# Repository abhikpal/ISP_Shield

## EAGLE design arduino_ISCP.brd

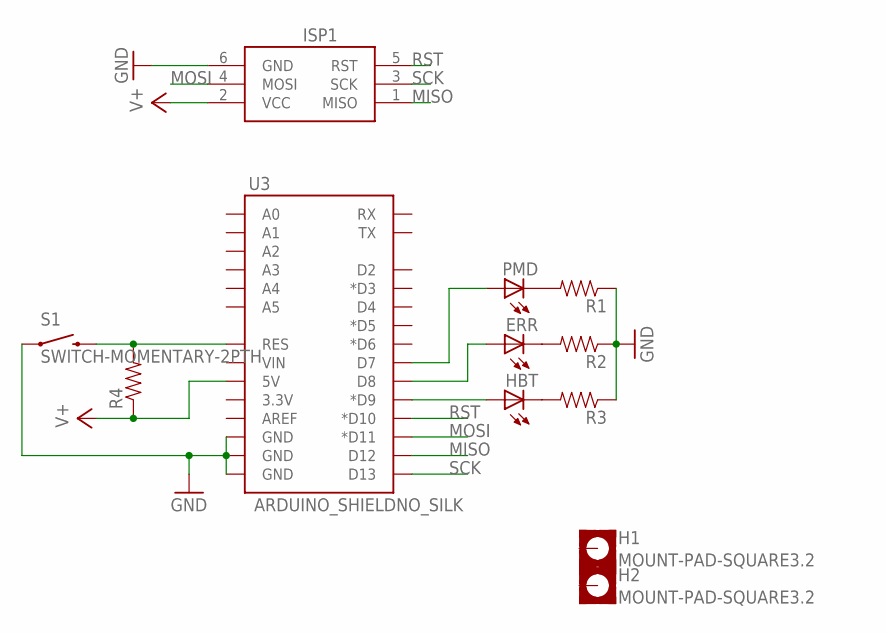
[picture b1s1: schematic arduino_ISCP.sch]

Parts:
ERR: LED5MM
H1, H2: MOUNT-PAD-SQUARE3.2; 3,2-PAD-SQUARE
HBT: LED5MM
ISP1: AVRISP-6; AVRISP
PMD: LED5MM
R1, R2, R3, R4: RESISTORPTH-1/4W; AXIAL-0.4
S1: SWITCH-MOMENTARY-2PTH; TACTILE-PTH
U3: ARDUINO_SHIELDNO_SILK; DUEMILANOVE_VIAS

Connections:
GND: ISP1.6 (GND), R1.P$1 (1), R2.P$1 (1), R3.P$1 (1), S1.1, U3.GND@0 (GND), U3.GND@1 (GND), U3.GND@2 (GND)
MISO: ISP1.1 (MISO), U3.D12
MOSI: ISP1.4 (MOSI), U3.D11 (*D11)
unnamed: R4.P$2 (2), S1.3 (2), U3.RES
unnamed: HBT.A, U3.D9 (*D9)
unnamed: ERR.A, U3.D8
unnamed: PMD.A, U3.D7
unnamed: PMD.K (C), R1.P$2 (2)
unnamed: ERR.K (C), R2.P$2 (2)
unnamed: HBT.K (C), R3.P$2 (2)
RST: ISP1.5 (RST), U3.D10 (*D10)
SCK: ISP1.3 (SCK), U3.D13
V+: ISP1.2 (VCC), R4.P$1 (1), U3.5V

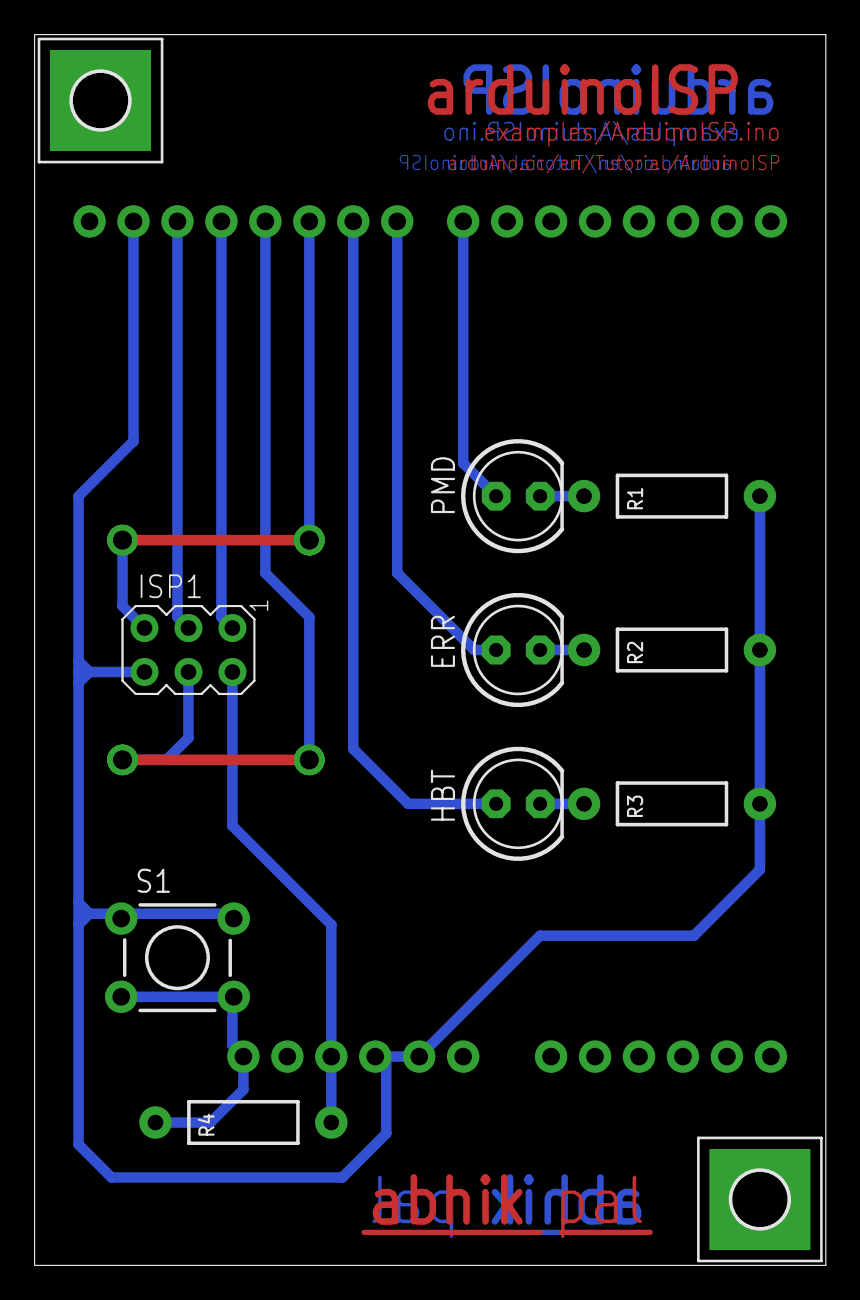
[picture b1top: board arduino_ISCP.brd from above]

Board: 2 copper layers, 45.7 x 71.1 mm, 12 parts (0 on the bottom side), 13 nets.

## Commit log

2014-04-23 Initial Commit
    The very first Arduino ISP shield schematics, board files and printable
    PNGs.

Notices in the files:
parts and their libraries:
SparkFun-Boards: Licensing: CC v3.0 Share-Alike You are welcome to use this library for commercial purposes.
